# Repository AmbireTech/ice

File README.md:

# Ambire Ice

A Safe-owner signing device: STM32U585 + two secure elements from two vendors,
NXP SE050 and Infineon OPTIGA Trust M, BLE behind a hardware airgap switch, QR
camera, 2.4" capacitive touch display, see-through case. Open hardware; the
firmware starts from a fork of Trezor's.

*Render of the 3D model: the board's back face through the case, with the flame
in silkscreen. The front (screen side) carries no brand at all.*

## Get one

**[ambire.com/ice](https://ambire.com/ice)**: the hardware wallet built for Safe.

- **Batch 2: $159**, limited to 200 devices. Reserve with a **$10 deposit**, which
  counts toward the price. Batch 1 (200 devices) is sold out.
- Delivery expected **within 6 months** of reserving.
- Four colours: Ice Blue, Orange Crush, Atomic Purple, Crystal Clear.
- A Safe signer over USB, Bluetooth or QR. It decodes every Safe action on screen
  (clear signing), blocks unknown DELEGATECALLs, and is ready for a post-quantum key
  on your Safe once chains support it.
- An airgap switch cuts USB data and radio power in hardware; offline, it signs
  over animated QR codes.
- Or build your own: the Gerber, BOM and pick-and-place files for JLCPCB or PCBWay
  are in this repo, and the case, battery-pack tray, joystick cap and airgap slider
  print on a home 3D printer.

Pictures on the site are illustrative; the shipped device may differ in shape and
colour.

**Built to be opened.** The clear case lets you see the board, but you don't
have to take our word for what's inside. Ice is designed to come apart and go
back together at home: undo one small M2 screw and the front hooks off; the
screen lifts off its foam tape and the battery pack comes away from its magnets.
Open it, compare the board with the files in this repo, and close it again.

Hand-routed by [@Ivshti](https://github.com/Ivshti), but component placement is
verified and optimized with
[humanizedKicadAutoRouter](https://github.com/Ivshti/humanizedKicadAutoRouter)
and [KiCadRoutingTools](https://github.com/drandyhaas/KiCadRoutingTools).

## Docs

- [docs/research.md](docs/research.md) — threat landscape 2024–2026, how the
  incumbents are built, why this architecture
- [docs/power-aaa.md](docs/power-aaa.md) — one AAA cell: which cells, how long
  they last, charging only NiMH, the power parts
- [docs/pack.md](docs/pack.md) — v4's battery pack: two AAA cells on a magnetic pogo
  connector pair, what JLC can build, what changes on the board
- [docs/design.md](docs/design.md) — the board, block by block, the case, and
  the bring-up checks that need parts in hand
- [docs/direction.md](docs/direction.md) — open hardware, starting from Trezor's
  firmware (what stands in the way), the configurator and the board print schemes
- [firmware/README.md](firmware/README.md) — the Trezor firmware port: build,
  flash, what changed, bring-up checks
- [docs/board-flow.md](docs/board-flow.md) — netlist → board → checks → order
  set: the commands and the order-time steps
- [art/README.md](art/README.md) — the back print: the flame silkscreen and the
  full-colour print for PCBWay
- [board/experiments/README.md](board/experiments/README.md) — placement
  candidates and how they were judged
- [docs/ambire-signer.html](docs/ambire-signer.html) — the concept page shared
  with the team (3D model, configurator with DIY downloads, clear signing,
  architecture, status); public copy: https://ambiretech.github.io/ice/
  (deployed by `.github/workflows/concept-page.yml`); the old Claude artifact
  link (https://claude.ai/artifact/LLUtmWoVMm4PUxiSL7d5Ad) now points there.
  That page shows proto 0 and stays as it is.
- [docs/v2/index.html](docs/v2/index.html) — the same page for proto 1 (the AAA
  cell, the joystick, the thinner case), with its own model and downloads:
  https://ambiretech.github.io/ice/v2/ (the proto 0 page does not link it)

## Firmware

Trezor's firmware, ported to this board: `firmware/trezor-firmware/` is
[trezor-firmware](https://github.com/trezor/trezor-firmware) with our changes on
top, started from `5fdc180` (2026-10-16). Every Monday a workflow pulls Trezor's
new commits from their `main` into this repo (Trezor → us; nothing goes back to
Trezor), keeps our changes on top, builds, and opens a PR here; the current base
is the first line of `firmware/vendor-pins.txt`. It builds as Trezor's T3T2
model with our own board, `ambire_p0`: our pin map, the display over SPI
(Trezor's is parallel), the FT5426 touch, and a power latch in the boardloader.
Development keys only, for the bench. The secure elements, radio, camera,
charger and battery gauge are not driven yet.

`firmware/docker-build.sh` builds it in Docker with Trezor's own toolchain.
Build, flashing, syncing with Trezor, the full list of changes and the bring-up
checks: [firmware/README.md](firmware/README.md). What is left and why:
[docs/direction.md](docs/direction.md#2-trezor-compatible-start-from-trezors-firmware).

## Board

The board is KiCad (`board/wallet.kicad_pcb`), with the netlist in tscircuit
(`index.circuit.tsx`, `src/blocks/`). How it is checked and turned into an
order: [docs/board-flow.md](docs/board-flow.md). The order set is in
`production/order/` (JLCPCB, and PCBWay for the full-colour back print).

## Similar projects

- [wedgie.dev](https://wedgie.dev)
- [Keycard Shell](https://keycard.tech/products/keycard-shell): an open-source,
  air-gapped signer around a Keycard smart card, with a camera for animated QR
  and no radio
- picowallet (Austin Griffith, 2026-09): the same key model, a P-256 key
  generated in an ATECC608 behind a vault contract, on an RP2350
  (see [docs/research.md](docs/research.md#competitive-notes))

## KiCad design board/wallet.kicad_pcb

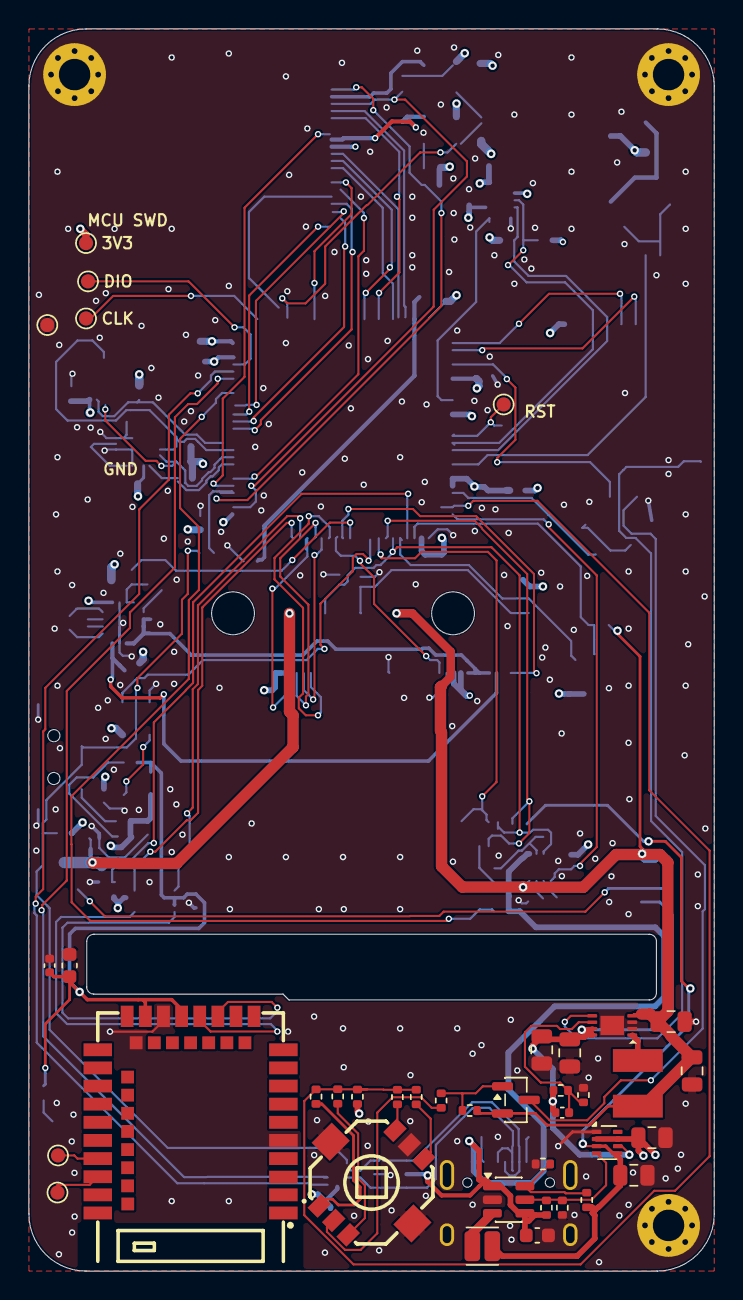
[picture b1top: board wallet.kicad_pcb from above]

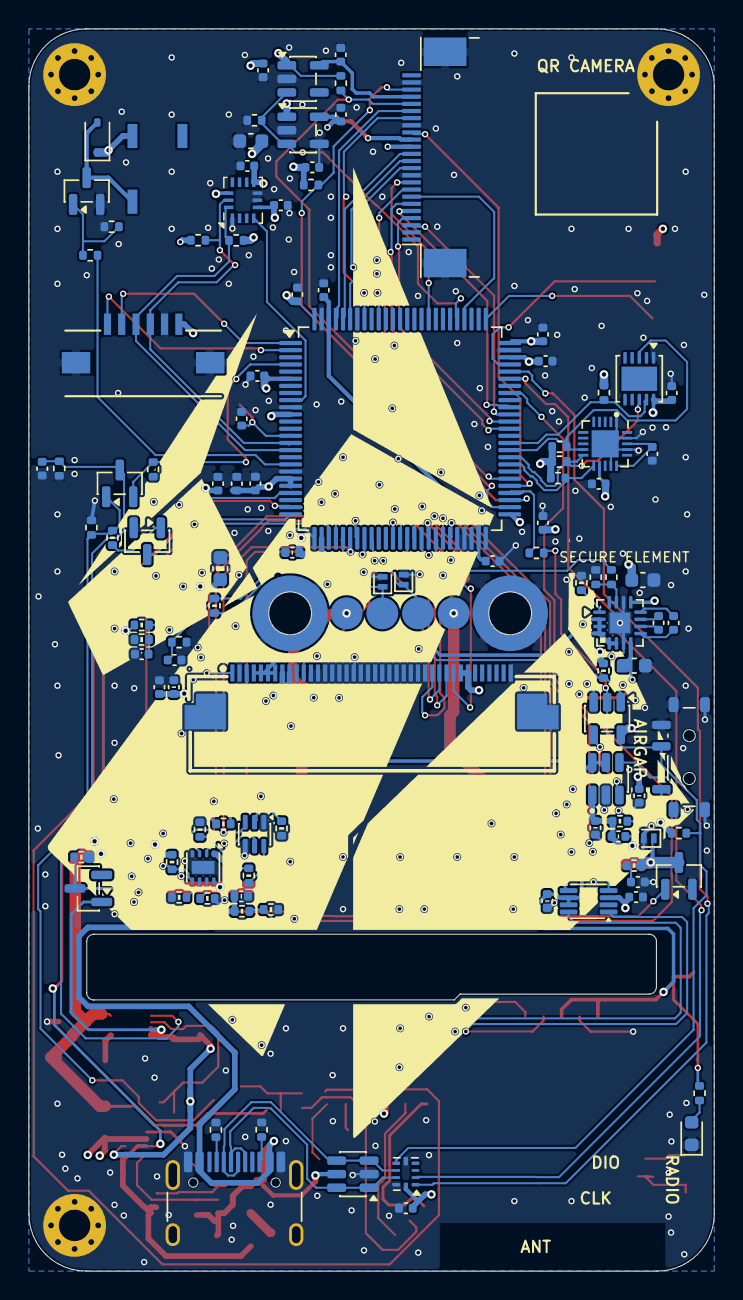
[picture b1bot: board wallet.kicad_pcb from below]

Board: 4 copper layers, 48.0 x 87.0 mm, 157 parts (116 on the bottom side), 108 nets.

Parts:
C_3V3: 22uF; C_0805_2012Metric
C_AVIN: 1uF; C_0402_1005Metric
C_AVOUT: 1uF; C_0402_1005Metric
C_BAT: 10uF; C_0805_2012Metric
C_BLF1, C_BLF2: 470nF; C_0402_1005Metric
C_BLIN: 1uF; C_0603_1608Metric
C_BLOUT: 1uF; C_0603_1608Metric
C_BOOST, C_BOOST2: 47uF; C_0805_2012Metric
C_BUZ: 10uF; C_0603_1608Metric
C_CHGIN: 1uF; C_0402_1005Metric
C_CNS: 100nF; C_0402_1005Metric
C_CS: 100nF; C_0402_1005Metric
C_DOVDD: 100nF; C_0402_1005Metric
C_DVOUT: 1uF; C_0402_1005Metric
C_EN: 1uF; C_0402_1005Metric
C_FFB: 33pF; C_0402_1005Metric
C_IMU1, C_IMU2: 100nF; C_0402_1005Metric
C_IN_BOOST: 22uF; C_0805_2012Metric
C_MS: 100nF; C_0402_1005Metric
C_NOR: 100nF; C_0402_1005Metric
C_NRST: 100nF; C_0402_1005Metric
C_OPT: 100nF; C_0402_1005Metric
C_RADIO1: 10uF; C_0603_1608Metric
C_RADIO2: 100nF; C_0402_1005Metric
C_RCT: 1nF; C_0402_1005Metric
C_RIN: 1uF; C_0402_1005Metric
C_SEIN: 100nF; C_0402_1005Metric
C_SEVCC: 100nF; C_0402_1005Metric
C_TFT1: 1uF; C_0402_1005Metric
C_TFT2: 100nF; C_0402_1005Metric
C_U9A, C_U9B: 100nF; C_0402_1005Metric
C_USB3V3: 22uF; C_0805_2012Metric
C_USBSW: 100nF; C_0402_1005Metric
C_VBAT: 100nF; C_0402_1005Metric
C_VBUS: 4.7uF; C_0603_1608Metric
C_VDD1, C_VDD2, C_VDD3, C_VDD4, C_VDD5: 100nF; C_0402_1005Metric
C_VDD11A, C_VDD11B: 2.2uF; C_0402_1005Metric
C_VDDA1: 1uF; C_0402_1005Metric
C_VDDA2: 100nF; C_0402_1005Metric
C_VDDB: 10uF; C_0603_1608Metric
C_VUSB: 100nF; C_0402_1005Metric
D_BUZ: 1N4148WS; D_SOD-323
D_ESD: USBLC6-2SC6; SOT-23-6
D_OR: BAT54C,215; SOT-23
D_PKMID: PESD5V0S1BL,315; D_SOD-882
D_PKNEG: PESD5V0S1BL,315; D_SOD-882
D_PKNTC: PESD5V0S1BL,315; D_SOD-882
D_RADIO: KT-0603G; LED_0603_1608Metric
D_REVG: BAS116,215; SOT-23
H1, H2, H4: MountingHole_2.2mm_M2_Pad_Via
J1: TYPE-C-31-M-12; USB_C_Receptacle_HRO_TYPE-C-31-M-12_BoardEdge
J_CAM: AFC07-S24FCA-00; Jushuo_AFC07-S24FCA-00_1x24-1MP_P0.50_Horizontal
J_CTP: HC-FPC-1.0-6P-FH20; FPC_HC-FPC-1.0-6P-FH20
J_PK1: J_PK1; Pack_Contact_Pad_D2.235mm
J_PK2: J_PK2; Pack_Contact_Pad_D2.235mm
J_PK3: J_PK3; Pack_Contact_Pad_D2.235mm
J_PK4: J_PK4; Pack_Contact_Pad_D2.235mm
J_TFT: 54132-4062; Molex_54132-4062
LS1: MLT-5020; Buzzer_Huaneng_MLT-5020_5x5.5mm
L_BOOST: WPN4020H2R2MT; L_Sunlord_WPN4020
L_BUCK: CKCSA201610-2.2uH/M; L_Cenker_CKCS201610
MH_PK1, MH_PK2: 9774015243R; Wurth_WA-SMSI_M2_L1.5
Q_BTN: MMBT3904; SOT-23
Q_BUZ: AO3416; SOT-23
Q_CHG: 2N7002DW-7-F; SOT-363_SC-70-6
Q_PWRJ: MMBT3906; SOT-23
Q_REV: AO3416; SOT-23
R_AIRPU: 100k; R_0402_1005Metric
R_AIRS: 1M; R_0402_1005Metric
R_AIRSER: 1k; R_0402_1005Metric
R_BLEN: 1k; R_0402_1005Metric
R_BLPD: 100k; R_0402_1005Metric
R_BLSET: 6.8k; R_0402_1005Metric
R_BTN: 100k; R_0402_1005Metric
R_BTNB: 100k; R_0402_1005Metric
R_BUZG: 100; R_0402_1005Metric
R_BUZPD: 100k; R_0402_1005Metric
R_CAMEN: 100k; R_0402_1005Metric
R_CC1, R_CC2: 5.1k; R_0402_1005Metric
R_CHGHI: 100k; R_0402_1005Metric
R_CHGOFF: 100k; R_0402_1005Metric
R_CNS: 100k; R_0402_1005Metric
R_CS1, R_CS2: 1M; R_0402_1005Metric
R_CSCL: 4.7k; R_0402_1005Metric
R_CSDA: 4.7k; R_0402_1005Metric
R_EN: 1M; R_0402_1005Metric
R_FB1: 1M; R_0402_1005Metric
R_FB2: 562k; R_0402_1005Metric
R_FBU1: 150k; R_0402_1005Metric
R_FBU2: 33k; R_0402_1005Metric
R_HOLD: 1M; R_0402_1005Metric
R_ISET: 3.6k; R_0402_1005Metric
R_ISETH: 1.8k; R_0402_1005Metric
R_JA: 15k; R_0402_1005Metric
R_JB: 27k; R_0402_1005Metric
R_JC: 47k; R_0402_1005Metric
R_JD: 100k; R_0402_1005Metric
R_JPU: 15k; R_0402_1005Metric
R_MS1, R_MS2: 1M; R_0402_1005Metric
R_OPTRST: 100k; R_0402_1005Metric
R_PG: 150k; R_0402_1005Metric
R_PGB: 100k; R_0402_1005Metric
R_PWRJB: 100k; R_0402_1005Metric
R_PWRJBE: 1M; R_0402_1005Metric
R_REVG: 1M; R_0402_1005Metric
R_RLED: 1k; R_0402_1005Metric
R_ROFF: 100k; R_0402_1005Metric
R_SCL: 4.7k; R_0402_1005Metric
R_SDA: 4.7k; R_0402_1005Metric
R_SEENA: 100k; R_0402_1005Metric
R_SESCL: 4.7k; R_0402_1005Metric
R_SESDA: 4.7k; R_0402_1005Metric
R_STAT: 10k; R_0402_1005Metric
R_TMR: 36k; R_0402_1005Metric
R_VB1: 47k; R_0402_1005Metric
R_VB2: 100k; R_0402_1005Metric
R_VSET: 36k; R_0402_1005Metric
SW_AIR: MSK12C02; SW_SPDT_Shouhan_MSK12C02
SW_JOY: SKRHAAE010; SW_ALPS_SKRHAAE010
TP_3V3: TP_3V3; TestPoint_Pad_D1.0mm
TP_GND: TP_GND; TestPoint_Pad_D1.0mm
TP_NRST: TP_NRST; TestPoint_Pad_D1.0mm
TP_RSWCLK: TP_RSWCLK; TestPoint_Pad_D1.0mm
TP_RSWDIO: TP_RSWDIO; TestPoint_Pad_D1.0mm
TP_SWCLK: TP_SWCLK; TestPoint_Pad_D1.0mm
TP_SWDIO: TP_SWDIO; TestPoint_Pad_D1.0mm
U1: BQ25172DSGR; WSON-8-1EP_2x2mm_P0.5mm_EP0.9x1.6mm
U2: LTC3539EDCB-2#TRPBF; LT_DCB8_DFN-8-1EP_2x3mm_P0.45mm
U3: TLV62569PDDCR; SOT-23-6
U4: STM32U585VIT6Q; LQFP-100_14x14mm_P0.5mm
U5: SE050E2HQ1/Z01Z3Z; NXP_SOT1969-1_HX2QFN-20_3x3mm_P0.4mm
U6: TS3USB221ARSER; Texas_UQFN-10_1.5x2mm_P0.5mm
U7: SN74LVC1G02DBVR(UMW); SOT-23-5
U8: TPS22917DBVR; SOT-23-6_PinMarkSouth
U9: TXU0202DCUR; VSSOP-8_2.3x2mm_P0.5mm
U10: TPS2116DRLR; SOT-583-8
U11: E73-2G4M08S1C; Ebyte_E73-2G4M08S1C
U12: ME6211C28M5G-N; SOT-23-5
U13: TPS60230RGTR; VQFN-16-1EP_3x3mm_P0.5mm_EP1.45x1.45mm
U14: TLV70312DBVR; SOT-23-5
U15: BMI270; Bosch_LGA-14_3x2.5mm_P0.5mm
U16: SLS32AIA010MK; DFN-10-1EP_3x3mm_P0.5mm_EP1.7x2.5mm

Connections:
AIRGAP: R_AIRPU.1, R_AIRS.1, SW_AIR.2, U6.6, U7.2
AIRGAP_SENSE: R_AIRS.2, U4.54
AIR_THROW: R_AIRSER.1, SW_AIR.1
BAT: C_BAT.1, C_IN_BOOST.1, J_PK1.1, L_BOOST.1, Q_PWRJ.2, R_CS1.1, R_PWRJBE.1, R_REVG.1, U1.8, U2.4
BAT_N: D_PKNEG.1, J_PK4.1, Q_REV.3, R_CNS.1
BL_A: C_BLOUT.1, J_TFT.3, U13.8
BL_C1N: C_BLF1.2, U13.11
BL_C1P: C_BLF1.1, U13.10
BL_C2N: C_BLF2.2, U13.12
BL_C2P: C_BLF2.1, U13.9
BL_EN: R_BLEN.2, R_BLPD.1, U13.15, U13.16
BL_ISET: R_BLSET.1, U13.1
BL_K: J_TFT.4, J_TFT.5, J_TFT.6, J_TFT.7, U13.2, U13.3, U13.4, U13.5, U13.6
BTN: D_OR.1, Q_PWRJ.3, R_BTN.1, R_BTNB.1
BTN_B: Q_BTN.1, R_BTNB.2
BTN_N: Q_BTN.3, U4.22
BUZZER: R_BUZG.1, U4.18
BUZ_G: Q_BUZ.1, R_BUZG.2, R_BUZPD.1
BUZ_SW: D_BUZ.2, LS1.2, Q_BUZ.3
CAM_AVDD: C_AVOUT.1, J_CAM.21, U12.5
CAM_D0: J_CAM.6, U4.63
CAM_D1: J_CAM.4, U4.64
CAM_D2: J_CAM.3, U4.65
CAM_D3: J_CAM.5, U4.66
CAM_D4: J_CAM.7, U4.79
CAM_D5: J_CAM.9, U4.84
CAM_D6: J_CAM.11, U4.95
CAM_D7: J_CAM.13, U4.96
CAM_DVDD: C_DVOUT.1, J_CAM.15, U14.5
CAM_EN: R_CAMEN.1, U4.80, U12.3, U14.3
CAM_HREF: J_CAM.16, U4.55
CAM_PCLK: J_CAM.8, U4.56
CAM_RST: J_CAM.19, U4.97
CAM_SCL: J_CAM.20, R_CSCL.1, U4.52
CAM_SDA: J_CAM.22, R_CSDA.1, U4.53
CAM_VSYNC: J_CAM.18, U4.93
CAM_XCLK: J_CAM.12, U4.91
CC1: J1.A5, R_CC1.1
CC2: J1.B5, R_CC2.1
CELL_MID: D_PKMID.1, J_PK2.1, R_MS1.1
CELL_MID_SENSE: C_MS.1, R_MS1.2, R_MS2.1, U4.30
CELL_N_SENSE: C_CNS.1, R_CNS.2, U4.29
CELL_SENSE: C_CS.1, R_CS1.2, R_CS2.1, U4.28
CHG_HI: Q_CHG.2, R_CHGHI.1, U4.33
CHG_ISET: R_ISET.1, R_ISETH.1, U1.2
CHG_ISETH: Q_CHG.6, R_ISETH.2
CHG_OFF: Q_CHG.5, R_CHGOFF.1, U4.32
CHG_STAT: R_STAT.1, U1.5, U4.25
CHG_TMR: R_TMR.1, U1.6
CHG_TS: D_PKNTC.1, J_PK3.1, Q_CHG.3, U1.3, U4.31
CHG_VSET: R_VSET.1, U1.7
CTP_INT: J_CTP.5, U4.1
CTP_RST: J_CTP.6, U4.2
FB_BOOST: C_FFB.2, R_FB1.2, R_FB2.1, U2.6
FB_USB: R_FBU1.2, R_FBU2.1, U3.6
GND: C_3V3.2, C_AVIN.2, C_AVOUT.2, C_BAT.2, C_BLIN.2, C_BLOUT.2, C_BOOST.2, C_BOOST2.2, C_BUZ.2, C_CHGIN.2, C_CNS.2, C_CS.2, C_DOVDD.2, C_DVOUT.2, C_EN.2, C_IMU1.2, C_IMU2.2, C_IN_BOOST.2, C_MS.2, C_NOR.2, C_NRST.2, C_OPT.2, C_RADIO1.2, C_RADIO2.2, C_RIN.2, C_SEIN.2, C_SEVCC.2, C_TFT1.2, C_TFT2.2, C_U9A.2, C_U9B.2, C_USB3V3.2, C_USBSW.2, C_VBAT.2, C_VBUS.2, C_VDD1.2, C_VDD2.2, C_VDD3.2, C_VDD4.2, C_VDD5.2, C_VDD11A.2, C_VDD11B.2, C_VDDA1.2, C_VDDA2.2, C_VDDB.2, C_VUSB.2, D_ESD.2, D_PKMID.2, D_PKNEG.2, D_PKNTC.2, D_RADIO.1, H1.1, H2.1, H4.1, J1.A1, J1.A12, J1.B1, J1.B12, J1.SH, J_CAM.10, J_CAM.17, J_CAM.23, J_CAM.MP, J_CTP.2, J_CTP.7, J_CTP.8, J_TFT.2, J_TFT.10, J_TFT.12, J_TFT.13, J_TFT.14, J_TFT.15, J_TFT.16, J_TFT.17, J_TFT.18, J_TFT.19, J_TFT.20, J_TFT.21, J_TFT.22, J_TFT.23, J_TFT.24, J_TFT.25, J_TFT.26, J_TFT.27, J_TFT.28, J_TFT.40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
I2C_SCL: J_CTP.3, R_SCL.1, U4.15, U15.13
I2C_SDA: J_CTP.4, R_SDA.1, U4.16, U15.14
IMU_INT: U4.9, U15.4
JOY_A: R_JA.2, SW_JOY.1
JOY_B: R_JB.2, SW_JOY.4
JOY_C: R_JC.2, SW_JOY.3
JOY_CEN: R_PWRJB.2, SW_JOY.2
JOY_D: R_JD.2, SW_JOY.6
JOY_DIR: R_JA.1, R_JB.1, R_JC.1, R_JD.1, R_JPU.2, U4.24
NRST: C_NRST.1, TP_NRST.1, U4.14
OPTIGA_RST: R_OPTRST.1, U4.61, U16.9
PWRJ_B: Q_PWRJ.1, R_PWRJB.1, R_PWRJBE.2
PWR_EN: C_EN.1, D_OR.3, R_EN.1, U2.5
PWR_HOLD: D_OR.2, R_HOLD.1, U4.4
RADIO_3V3: C_RADIO1.1, C_RADIO2.1, C_U9B.1, R_RLED.1, U8.5, U8.6, U9.6, U9.7, U11.19, U11.23
RADIO_CT: C_RCT.2, U8.4
RADIO_EN: U7.4, U8.3
RADIO_LED_A: D_RADIO.2, R_RLED.2
RADIO_OFF: R_ROFF.1, U4.34, U7.1
RADIO_RX: U9.8, U11.15
RADIO_RXD_MCU: U4.45, U9.4
RADIO_SWCLK: TP_RSWCLK.1, U11.39
RADIO_SWDIO: TP_RSWDIO.1, U11.37
RADIO_TX: U9.1, U11.17
RADIO_TXD_MCU: U4.44, U9.5
REV_G: D_REVG.3, Q_REV.1, R_REVG.2
SE_ENA: R_SEENA.1, U4.58, U5.11
SE_SCL: R_SESCL.1, U4.59, U5.10, U16.8
SE_SDA: R_SESDA.1, U4.60, U5.9, U16.3
SE_VCC: C_SEVCC.1, U5.15, U5.18
SWCLK: TP_SWCLK.1, U4.76
SWDIO: TP_SWDIO.1, U4.72
SW_BOOST: L_BOOST.2, U2.1
SW_USB: L_BUCK.1, U3.3
TFT_BL: R_BLEN.1, U4.37
TFT_CS: J_TFT.31, U4.42
TFT_DC: J_TFT.29, U4.40
TFT_MOSI: J_TFT.32, U4.43
TFT_RST: J_TFT.11, U4.39
TFT_SCK: J_TFT.30, U4.41
TFT_TE: J_TFT.1, U4.38
USB_DN: D_ESD.3, D_ESD.4, J1.A7, J1.B7, U6.7
USB_DP: D_ESD.1, D_ESD.6, J1.A6, J1.B6, U6.8
USB_MCU_DN: U4.70, U6.2
USB_MCU_DP: U4.71, U6.1
USB_PG: R_PG.1, R_PGB.1, U3.5, U10.4
V3V3: C_3V3.1, C_AVIN.1, C_BLIN.1, C_BUZ.1, C_DOVDD.1, C_IMU1.1, C_IMU2.1, C_NOR.1, C_OPT.1, C_RCT.1, C_RIN.1, C_SEIN.1, C_TFT1.1, C_TFT2.1, C_U9A.1, C_USBSW.1, C_VBAT.1, C_VDD1.1, C_VDD2.1, C_VDD3.1, C_VDD4.1, C_VDD5.1, C_VDDA1.1, C_VDDA2.1, C_VDDB.1, C_VUSB.1, D_BUZ.1, J_CAM.14, J_CTP.1, J_TFT.8, J_TFT.9, J_TFT.33, J_TFT.34, LS1.1, R_AIRPU.2, R_AIRSER.2, R_CSCL.2, R_CSDA.2, R_JPU.1, R_OPTRST.2, R_ROFF.2, R_SCL.2, R_SDA.2, R_SEENA.2, R_SESCL.2, R_SESDA.2, R_STAT.2, TP_3V3.1, U4.6, U4.11, U4.20, U4.21, U4.27, U4.51, U4.73, U4.75, U4.100, U5.12, U6.10, U7.5, U8.1, U9.3, U10.2, U10.7, U12.1, U13.13, U14.1, U15.5, U15.8, U15.12, U16.10
V3V3_USB: C_USB3V3.1, L_BUCK.2, R_CHGOFF.2, R_FBU1.1, U10.3, U10.5
VBUS: C_CHGIN.1, C_VBUS.1, D_ESD.5, J1.A4, J1.A9, J1.B4, J1.B9, R_PG.2, R_VB1.1, U1.1, U3.1, U3.4
VBUS_SENSE: R_VB1.2, R_VB2.1, U4.68
VDD11: C_VDD11A.1, C_VDD11B.1, U4.49, U4.98
V_BOOST: C_BOOST.1, C_BOOST2.1, C_FFB.1, D_REVG.1, R_FB1.1, U2.7, U2.8, U10.6

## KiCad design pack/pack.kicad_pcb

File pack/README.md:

# The battery pack's board (v4)

Ambire Ice v4 runs from two AAA cells in a pack that snaps onto its back (why and how:
[../docs/pack.md](../docs/pack.md)). This is the pack's own board: the cells' clips on
one face, four spring pins and the seats of two magnets on the other, the face toward the
device. The magnets, in a printed frame, hold the pack on two steel spacers on the device
board; the pins press on four gold target discs there.

48.0 × 26.6 mm, 2 layers, 0.8 mm thick, ENIG, routed.

*Rendered by KiCad: the outer face (toward the device), and the inner face seen from
behind, mirrored.*

## What is on it

| Part | Face | JLC / LCSC |
|---|---|---|
| Xinyangze YZP0058-20048-02, spring pin, SMD with a peg (1 A) ×4 | outer | C5157341 |
| Radial Magnets 8063, NdFeB N40 magnet, 3.18 × 3.18 mm ×2 (glued into the frame, not assembled by JLC) | outer | DigiKey 469-8063-ND |
| MYOUNG MY-AAA-19-J, AAA clip (−, spring) ×2 | inner | C6937104 |
| MYOUNG MY-AAA-20-J, AAA clip (+) ×2 | inner | C6937107 |
| BHFUSE BSMD1206-075-30V, resettable fuse, 0.75 A hold | inner | C976305 |
| Murata NCP18XH103F03RB, 10 k thermistor (B 3380 K), 0603 | inner | C13564 |
| 1 k resistor, 0402 | inner | C11702 |

The two cells are in series: the south cell's plus goes through the fuse to the BAT+
pin; its minus meets the north cell's plus at the west clips (the mid-point, MID),
which reaches its pin through the 1 k resistor; the north cell's minus is BAT−. The
thermistor sits between the NTC pin and BAT−, for the charger's temperature input. A
coin across the pins never shorts a cell hard: plus to minus runs through the fuse, any
short to MID through the 1 k resistor.

The outer face carries only the pins, the frame's two peg holes, the mid-point's run under
the frame and a BAT− pour. The magnets stand on it over the device's steel, in the
frame's pockets. The pin order lives in one place, `PIN_NETS` in `makePack.py`.

**Where the contacts go.** Over the device's discs and spacers, which lie east-west south
of the device's MCU (x 22.0, y 42.28 in device board coordinates): along the south cell,
the frame's tab east, the four pins in a row under the cell's south flank, plus at the
east end. The clips hold only the cells' ends, so the holes are 5.6 mm from any of their steel, and
the cells lie side by side, 12.8 mm apart: 1.8 mm between neighbouring clips' arms, twice
the ~0.9 mm each arm swings out as a cell goes in (on the east side those arms are the
pack's minus and the south cell's plus, ahead of the fuse). `makePack.py` reads the
contacts' place, the magnets and the clips' steel from the case (`enclosure.json`) and
refuses a hole within 0.3 mm of the steel.

**The small parts** sit in the strip south of the south cell's can, where nothing stands
over them, each straddling its pin's line: the thermistor between BAT− and NTC, the 1 k
resistor at MID, the fuse east of BAT+. The mid-point reaches the resistor from the
south-west clip on the outer face, under the frame.

**The pins' land** is JLC's own (EasyEDA's for C5157341): four quadrant pads in a 2.0 mm
square round a plated hole for the pin's 0.40 mm peg. The hole is 0.50 mm here (EasyEDA
draws 0.40, no room for the peg), with a 1.30 mm ring that joins the quadrants in copper.
Plated, the hole carries each pin to the inner face, where its run starts. The frame's
footprint (`Pack_Frame`, written by `makePack.py`) is its two 1.1 mm peg holes, with the
outline and the magnets on F.Fab; it is out of the BOM and the CPL. The pin's 3D model
(`3d/`, by `connModel.py`) is drawn from Xinyangze's drawing (2015-05-14).

## Files

- `pack.kicad_pcb`, `pack.kicad_pro`: the board and its rules (Power class 0.8 mm for the
  cells, the fuse and the pins; 0.25 mm for the sense lines).
- `makePack.py`: builds the board from scratch from `docs/v4/enclosure/enclosure.json`
  (outline, cells, contacts, magnets, frame) and its own constants (the parts, the copper). After a
  hand edit, edit the board instead.
- `../production/boardOrder.py`: writes `../production/pack-order/` (Gerbers and drill zip,
  JLC BOM and CPL, `stock.txt` with JLC's live stock).

```sh
KICAD_PY=/Applications/KiCad/KiCad.app/Contents/Frameworks/Python.framework/Versions/Current/bin/python3
$KICAD_PY pack/makePack.py                                  # the board (overwrites it)
kicad-cli pcb drc --severity-all pack/pack.kicad_pcb        # as saved, and again with --refill-zones
$KICAD_PY production/boardOrder.py pack/pack.kicad_pcb production/pack-order pack 200   # the order files
```

## Ordering at JLC

- **Assembly:** SMT on **both** faces: the pins on the outer face (top), the clips, the
  fuse, the thermistor and the resistor on the inner face (bottom).
- **Stock:** the pins have 1,216 at JLC (2026-11-01): 304 packs. `stock.txt` marks any
  part whose stock covers fewer than 200 packs as SHORT. The magnets come from DigiKey.
- **Rotations:** check every part in JLC's placement preview before paying. The clips
  carry the same rotation as the device board's (the south cell's exactly so, the
  north cell's turned 180°); the pins are round, so their rotation does not matter. The CPL's rotations are KiCad's, not confirmed by JLC.
- The board is 0.8 mm thick and ENIG: pick both in the order form.

What the checks cover: DRC at every severity (none found, with and without a zone
refill), full connectivity, no stale copper. What they do not: the magnets' hold on the
device's steel spacers and the pins' contact on its discs, the glue, the clips holding cells on a 0.8 mm board, the fuse's heating at full
load, the fit in the tray. These files have not been ordered yet.

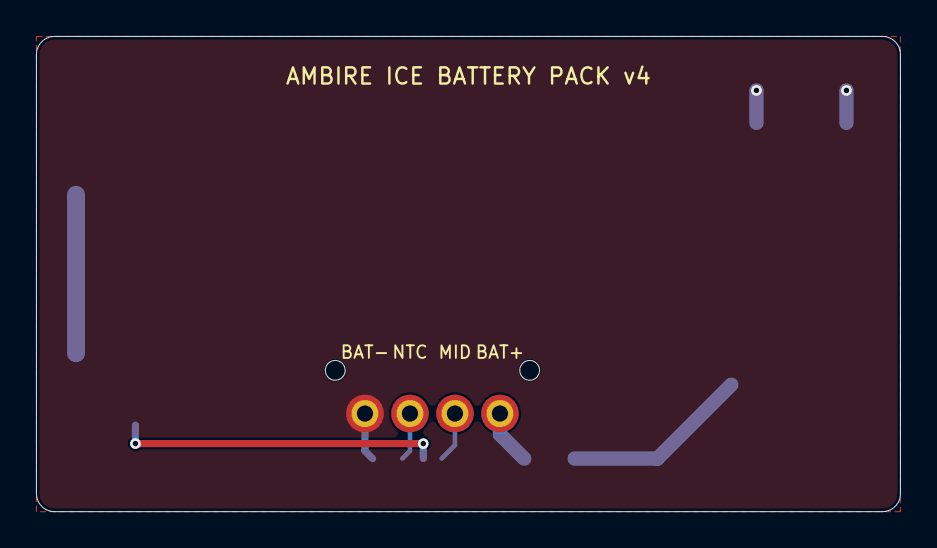
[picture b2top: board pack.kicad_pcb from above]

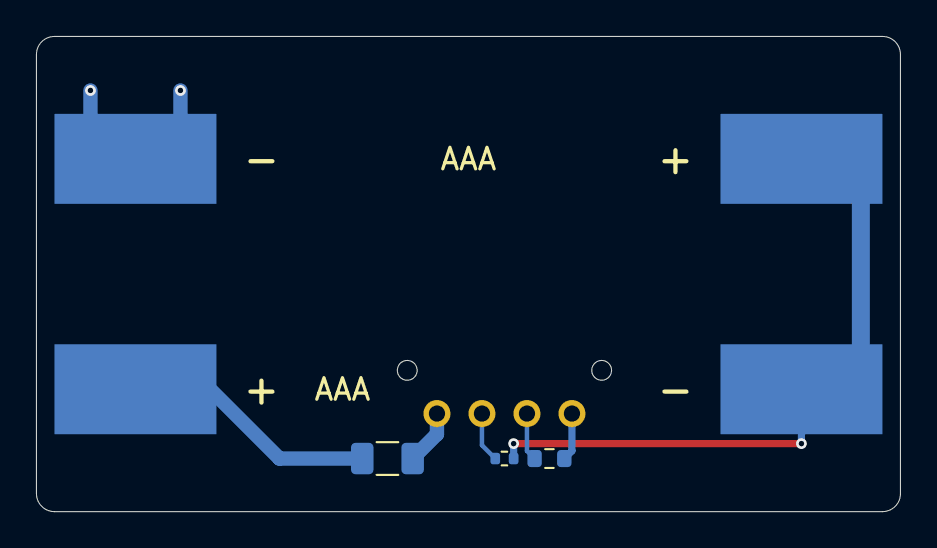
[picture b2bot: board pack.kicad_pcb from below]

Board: 2 copper layers, 48.0 x 26.4 mm, 12 parts (7 on the bottom side), 6 nets.

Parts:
BT_N1, BT_N2: MY-AAA-19-J; Battery_AAA_Clip_MYOUNG_MY-AAA-19-J
BT_P1, BT_P2: MY-AAA-20-J; Battery_AAA_Clip_MYOUNG_MY-AAA-20-J
FR1: frame (print); Pack_Frame
F_BAT: 0.75A hold; Fuse_1206_3216Metric
J_PACK1, J_PACK2, J_PACK3, J_PACK4: YZP0118-20063-02; Xinyangze_YZP0118-20063-02
RT_PACK: 10k NTC B3380; R_0603_1608Metric
R_MID: 1k; R_0402_1005Metric

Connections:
BAT+: F_BAT.1, J_PACK4.1
BAT-: BT_N1.1, J_PACK1.1, RT_PACK.1
CELL+: BT_P2.1, F_BAT.2
MID: BT_N2.1, BT_P1.1, R_MID.1
MID_SENSE: J_PACK3.1, R_MID.2
NTC: J_PACK2.1, RT_PACK.2

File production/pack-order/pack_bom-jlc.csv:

Comment,Designator,Footprint,LCSC Part #
MY-AAA-19-J,"BT_N1,BT_N2",Battery_AAA_Clip_MYOUNG_MY-AAA-19-J,C6937104
MY-AAA-20-J,"BT_P1,BT_P2",Battery_AAA_Clip_MYOUNG_MY-AAA-20-J,C6937107
0.75A hold,F_BAT,Fuse_1206_3216Metric,C976305
YZR0158-20050-04025-01,J_PACK,Xinyangze_YZR0158-20050-04025-01,C5126843
10k NTC B3380,RT_PACK,R_0603_1608Metric,C13564
1k,R_MID,R_0402_1005Metric,C11702

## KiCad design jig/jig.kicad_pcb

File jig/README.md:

# Programming jig

A fixture that programs a bare, assembled device board over SWD, before the screen and
the case go on. One board, one USB-C cable to a computer; no separate debug probe.

The jig sits on a printed base, parts facing up, on four poles through its holes. The
device board goes on **face down**: three of the poles go through its corner holes and
carry it 5 mm above the jig, and seven spring pins press up into its programming pads (3.3 V, ground, SWDIO, SWCLK and reset for the MCU; SWDIO and
SWCLK for the radio). The jig is a USB debug probe: an RP2040 running Raspberry Pi's open
debugprobe firmware, which speaks CMSIS-DAP. It also powers the board while it is
programmed. The USB-C, the two switches and the two lights sit on a strip beside the
board, where they stay in reach and in sight.

The repo's SWD tool works with it as it is: `firmware/swd.py --probe cmsis-dap …`.

**Ordered on 2026-11-01** (the Gerbers of c593d1c). From then on the device board's
programming pads and its holes H1, H2, H4 are **frozen** where `jig/frozen.json` has them:
their footprints are locked in KiCad, and the device board's pre-fab checks fail if any of
them moves. Moving one means a new jig.

## What it is made of

| Part | How many | Where from |
|---|---|---|
| Jig board, 62 × 93 mm, 4 layers, 1.6 mm, parts on one face | 1 | JLC: `production/jig-order/` |
| Base: a plate with four poles | 1 | printed: `jig/out/base.stl` |
| Lid: rests on the board's three hole rings | 1 | printed: `jig/out/lid.stl` |
| A weight of about 300 g (a phone, a small bag of coins) | 1 | to hand |

Every electronic part is JLC stock. The seven spring pins (Xinyangze YZP0063-20068-01)
work at 5.0 mm, 25 g each.

## Putting it together

Print the base and the lid, ideally in resin (JLC3DP's SLA, or any resin printer): the
poles end in 2 mm pins. An FDM print works too, poles standing up, but the pins are
fragile. Drop the jig onto the base's four poles, parts face up: it rests on the poles'
wide feet. Nothing else holds it.

The weight is needed, not optional: the seven spring pins push up with about 175 g, and a
board weighs about 15 g. Without it the board floats on the pins, a millimetre above the
poles, touching its pads with almost no force.

## First use: load the probe's firmware

1. Download `debugprobe_on_pico.uf2` from Raspberry Pi's debugprobe releases
   (github.com/raspberrypi/debugprobe). The jig is wired exactly as that build expects.
2. Plug the jig into a computer. A new jig has an empty flash and shows up as a USB drive
   called RPI-RP2. Copy the file onto it. The drive disappears and the green USB light
   comes on: the probe is ready.
3. To load firmware again later, bridge the two BOOT pads (tweezers) while plugging in.
   Do it with no board on the jig: the pads are under it.

## Programming a board

1. Lay the board **face down** on the jig, its three corner holes over the three poles'
   pins. Put the lid on (its three holes over the same pins) and the weight on the lid.
2. Slide **TARGET 3V3** to ON. The red light shows the board is powered.
3. **The MCU:** selector to **MCU**, then for example

   ```sh
   firmware/swd.py --probe cmsis-dap info
   firmware/swd.py --probe cmsis-dap flash
   ```

4. **The radio** (after the MCU's firmware runs: the MCU switches the radio's power on):
   selector to **RADIO**, then `firmware/swd.py --probe cmsis-dap radio-info` and
   `radio-flash`.
5. TARGET 3V3 to OFF, weight and lid off, board out.

Keep TARGET 3V3 **off** whenever the board runs from its own battery pack or its own USB.

## Check once, on the first jig

- **Switch directions.** The labels assume a slide switch connects the side its knob is
  on. With the jig unplugged, check with a meter: selector at MCU, the SWDIO spring pin
  connects to the selector's middle pin; TARGET 3V3 at ON, the 3.3 V spring pin reads 3.3 V
  with USB in.
- **Registration.** Each spring pin's tip should land in the middle of its pad: look at
  the marks they leave on a first board. The poles locate both boards, so a print that is
  a little off moves them together; a pin that is loose in a hole is the thing to watch.
- **SWD speed.** `swd.py` defaults to 1 MHz for flying leads; on the jig a faster clock
  (`--khz 4000`) should work, untried.

## Making the board

```sh
KICAD_PY=/Applications/KiCad/KiCad.app/Contents/Frameworks/Python.framework/Versions/Current/bin/python3
$KICAD_PY jig/makeJig.py --check                           # do the device board's pads and holes still match?
$KICAD_PY jig/makeJig.py                                   # placed, planes drawn, not routed
$KICAD_PY ../../tools/humanRouter/run.py jig/jig.kicad_pcb --out /tmp/jigroute     # route it
$KICAD_PY scripts/tidyDefects.py /tmp/jigroute/jig.kicad_pcb jig/jig.kicad_pcb     # stubs out
kicad-cli pcb drc --severity-all jig/jig.kicad_pcb         # as saved, and again with --refill-zones
$KICAD_PY production/boardOrder.py jig/jig.kicad_pcb production/jig-order jig 5
../../.venv-enclosure/bin/python jig/makeFixture.py --check   # base and lid; overlaps with both boards
```

`makeJig.py` holds the jig's board: the probe's parts and nets and the pins over the
device's pads; `makeFixture.py` the printed base and lid; `geometry.py` the numbers both
share (the holes, the heights, the pole sizes). It overwrites the board. It first reads the
device board and refuses to build when a programming pad or one of the three holes has
moved, or when two pads sit closer than 2.5 mm (the pins' flanges): change the jig's
numbers to the board's, rebuild, route, and recut its order files.

## Ordering at JLC

- 4 layers, 1.6 mm, any colour; assembly on **one** face: every part is on the bottom
  layer (the parts face).
- Check every part's rotation in JLC's placement preview before paying: the RP2040's pin 1,
  the crystal, the two regulators, the USB-C, the ESD clamp, the two LEDs' polarity and
  both switches.
- The spring pins: JLC had 401 on 2026-11-01; one jig takes seven.

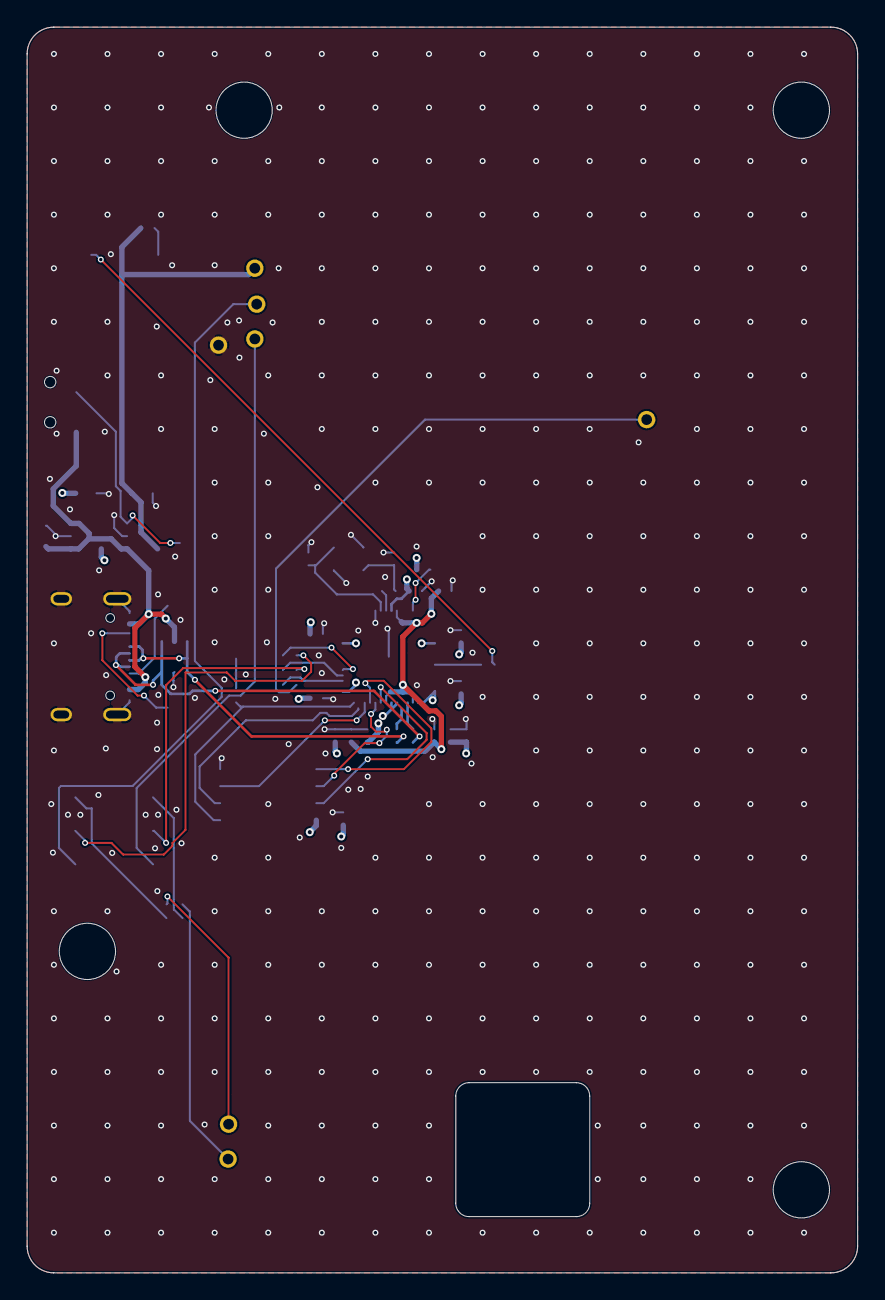
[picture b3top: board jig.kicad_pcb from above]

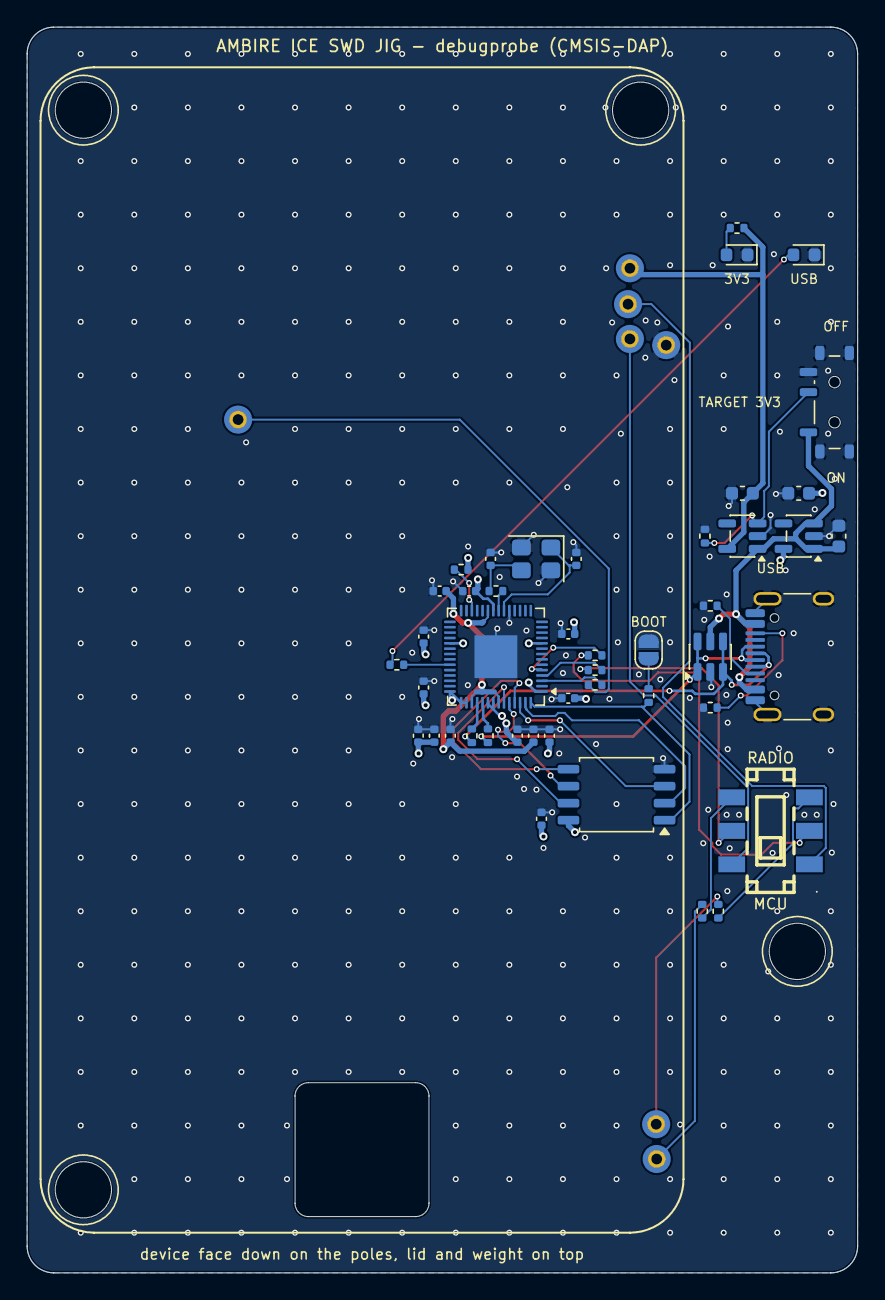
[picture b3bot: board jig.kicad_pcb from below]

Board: 4 copper layers, 62.0 x 93.0 mm, 56 parts (56 on the bottom side), 38 nets.

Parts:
C_3V3P: 10uF; C_0603_1608Metric
C_AV: 100nF; C_0402_1005Metric
C_DV23, C_DV50: 100nF; C_0402_1005Metric
C_FL: 100nF; C_0402_1005Metric
C_IO1, C_IO10, C_IO22, C_IO33, C_IO42, C_IO49: 100nF; C_0402_1005Metric
C_TGT: 10uF; C_0603_1608Metric
C_UV: 100nF; C_0402_1005Metric
C_VBUS: 10uF; C_0603_1608Metric
C_VRI: 1uF; C_0402_1005Metric
C_VRO: 1uF; C_0402_1005Metric
C_XI: 15pF; C_0402_1005Metric
C_XO: 15pF; C_0402_1005Metric
D_ESD: USBLC6-2SC6; SOT-23-6
D_TGT: red; LED_0603_1608Metric
D_USB: green; LED_0603_1608Metric
H_1, H_2, H_4, H_5: pole; Jig_Hole_Pole_4.2mm
JP_BOOT: SolderJumper-2_P1.3mm_Open_RoundedPad1.0x1.5mm
J_USB: TYPE-C-31-M-12; USB_C_Receptacle_HRO_TYPE-C-31-M-12_BoardEdge
P_3V3: YZP0063-20068-01; Xinyangze_YZP0063-20068-01
P_GND: YZP0063-20068-01; Xinyangze_YZP0063-20068-01
P_NRST: YZP0063-20068-01; Xinyangze_YZP0063-20068-01
P_RSWCLK: YZP0063-20068-01; Xinyangze_YZP0063-20068-01
P_RSWDIO: YZP0063-20068-01; Xinyangze_YZP0063-20068-01
P_SWCLK: YZP0063-20068-01; Xinyangze_YZP0063-20068-01
P_SWDIO: YZP0063-20068-01; Xinyangze_YZP0063-20068-01
R_BOOT: 1k; R_0402_1005Metric
R_CC1, R_CC2: 5.1k; R_0402_1005Metric
R_CE: 100k; R_0402_1005Metric
R_DN: 27; R_0402_1005Metric
R_DP: 27; R_0402_1005Metric
R_LT: 1k; R_0402_1005Metric
R_LU: 1k; R_0402_1005Metric
R_NRST: 1k; R_0402_1005Metric
R_RSWC: 1k; R_0402_1005Metric
R_RSWD: 1k; R_0402_1005Metric
R_RUN: 10k; R_0402_1005Metric
R_SWC: 100; R_0402_1005Metric
R_SWD: 100; R_0402_1005Metric
R_XO: 1k; R_0402_1005Metric
SW_PWR: MSK12C02; SW_SPDT_Shouhan_MSK12C02
SW_SEL: K3-2235S-K1; SW_DPDT_Hroparts_K3-2235S-K1
U1: RP2040; QFN-56-1EP_7x7mm_P0.4mm_EP3.2x3.2mm
U2: W25Q16JVSSIQ; SOIC-8_5.3x5.3mm_P1.27mm
U_LP: ME6211C33; SOT-23-5
U_LT: ME6211C33; SOT-23-5
Y1: 12MHz; Crystal_SMD_3225-4Pin_3.2x2.5mm

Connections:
BOOT_R: JP_BOOT.1, R_BOOT.2
CC1: J_USB.A5, R_CC1.1
CC2: J_USB.B5, R_CC2.1
CE_TGT: R_CE.1, SW_PWR.2, U_LT.3
GND: C_3V3P.2, C_AV.2, C_DV23.2, C_DV50.2, C_FL.2, C_IO1.2, C_IO10.2, C_IO22.2, C_IO33.2, C_IO42.2, C_IO49.2, C_TGT.2, C_UV.2, C_VBUS.2, C_VRI.2, C_VRO.2, C_XI.2, C_XO.2, D_ESD.2, D_TGT.1, D_USB.1, JP_BOOT.2, J_USB.A1, J_USB.A12, J_USB.B1, J_USB.B12, J_USB.SH, P_GND.1, R_CC1.2, R_CC2.2, R_CE.2, SW_PWR.3, SW_PWR.SH, U1.19, U1.57, U2.4, U_LP.2, U_LT.2, Y1.2, Y1.4
LED_TGT_A: D_TGT.2, R_LT.2
LED_USB: R_LU.1, U1.37
LED_USB_A: D_USB.2, R_LU.2
MCU_SWCLK: P_SWCLK.1, SW_SEL.6
MCU_SWDIO: P_SWDIO.1, SW_SEL.1
NRST: P_NRST.1, R_NRST.2
PRB_NRST: R_NRST.1, U1.3
PRB_SWCLK: R_SWC.1, U1.4
PRB_SWDIO: R_SWD.1, U1.5
QSPI_SCLK: U1.52, U2.6
QSPI_SD0: U1.53, U2.5
QSPI_SD1: U1.55, U2.2
QSPI_SD2: U1.54, U2.3
QSPI_SD3: U1.51, U2.7
QSPI_SS: R_BOOT.1, U1.56, U2.1
RAD_SWCLK: P_RSWCLK.1, R_RSWC.2
RAD_SWCLK_S: R_RSWC.1, SW_SEL.4
RAD_SWDIO: P_RSWDIO.1, R_RSWD.2
RAD_SWDIO_S: R_RSWD.1, SW_SEL.3
RUN: R_RUN.2, U1.26
SWCLK_P: R_SWC.2, SW_SEL.5
SWDIO_P: R_SWD.2, SW_SEL.2
USBR_DN: R_DN.2, U1.46
USBR_DP: R_DP.2, U1.47
USB_DN: D_ESD.3, D_ESD.4, J_USB.A7, J_USB.B7, R_DN.1
USB_DP: D_ESD.1, D_ESD.6, J_USB.A6, J_USB.B6, R_DP.1
V1V1: C_DV23.1, C_DV50.1, C_VRO.1, U1.23, U1.45, U1.50
V3V3_PROBE: C_3V3P.1, C_AV.1, C_FL.1, C_IO1.1, C_IO10.1, C_IO22.1, C_IO33.1, C_IO42.1, C_IO49.1, C_UV.1, C_VRI.1, R_RUN.1, U1.1, U1.10, U1.22, U1.33, U1.42, U1.43, U1.44, U1.48, U1.49, U2.8, U_LP.5
V3V3_TGT: C_TGT.1, P_3V3.1, R_LT.1, U_LT.5
VBUS: C_VBUS.1, D_ESD.5, J_USB.A4, J_USB.A9, J_USB.B4, J_USB.B9, SW_PWR.1, U_LP.1, U_LP.3, U_LT.1
XIN: C_XI.1, U1.20, Y1.1
XOUT: R_XO.1, U1.21
XOUT_R: C_XO.1, R_XO.2, Y1.3

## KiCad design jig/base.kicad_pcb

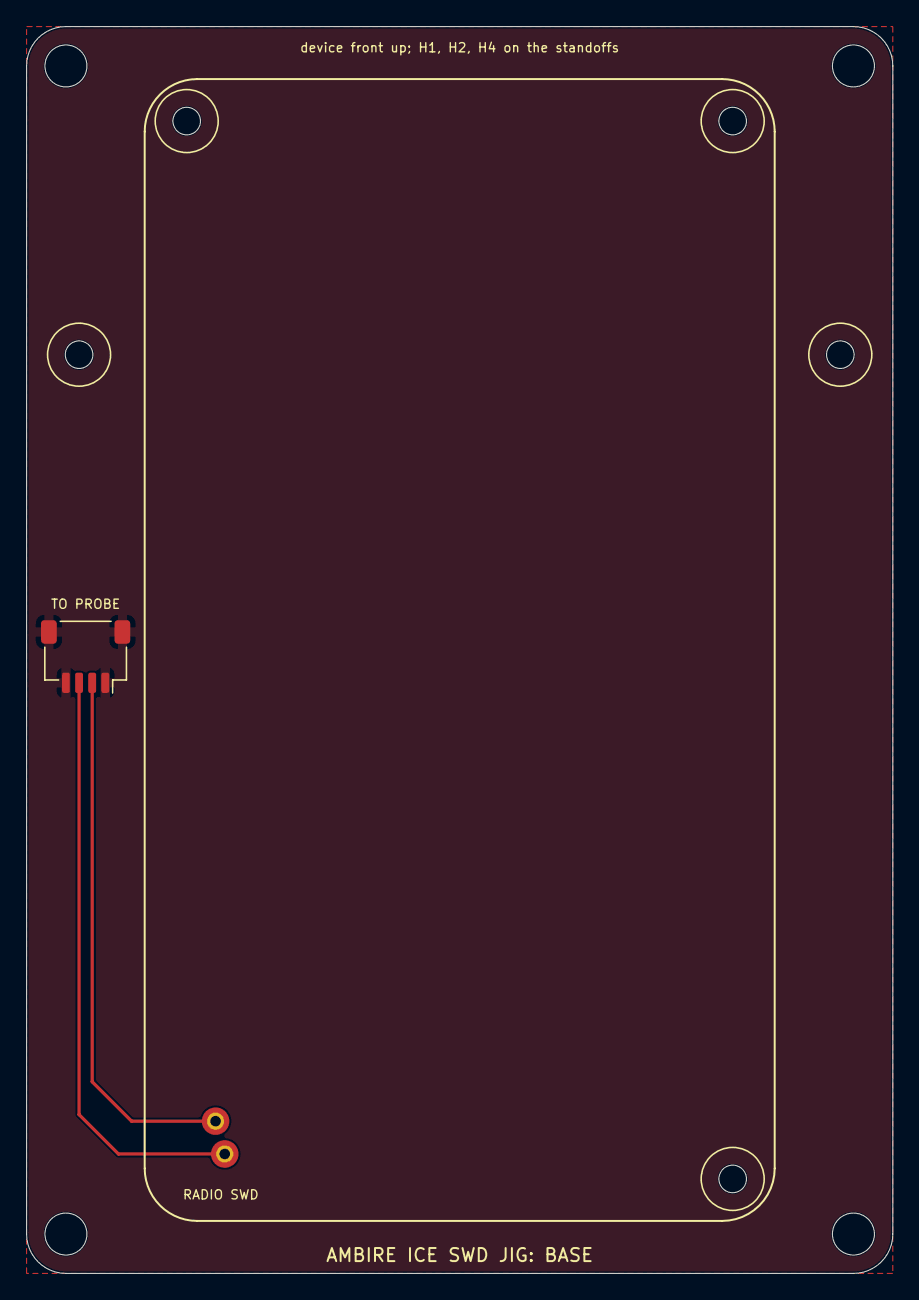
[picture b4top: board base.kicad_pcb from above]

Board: 2 copper layers, 66.0 x 95.0 mm, 12 parts (0 on the bottom side), 3 nets.

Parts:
H_1, H_2, H_4: M2 hole; Jig_Hole_M2_NPTH
H_F1, H_F2, H_F3, H_F4: M3 foot; Jig_Hole_M3_Foot
H_P1, H_P2: M2 hole; Jig_Hole_M2_NPTH
J_RAD: SM04B-SRSS-TB; JST_SH_SM04B-SRSS-TB_1x04-1MP_P1.00mm_Horizontal
P_RSWCLK: YZP0063-20068-01; Xinyangze_YZP0063-20068-01
P_RSWDIO: YZP0063-20068-01; Xinyangze_YZP0063-20068-01

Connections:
GND: J_RAD.1, J_RAD.4, J_RAD.MP
RAD_SWCLK: J_RAD.3, P_RSWCLK.1
RAD_SWDIO: J_RAD.2, P_RSWDIO.1

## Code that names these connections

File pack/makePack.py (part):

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  B (inner face): two AAA cells east-west in series, in MYOUNG clips copied from the
    device board (the south cell as proto 1's cell sat, + east; the north cell turned
    end for end, + west; the west clips are the mid-point); the fuse, the thermistor and
    the mid-point's series resistor beside the pins.

pcbnew: one LoadBoard per process. The board is started as a minimal file beside
pack.kicad_pro (so it gets the pack's rules), loaded once, built, zones filled, saved.
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CONN_PAD = 1.5                            # a pin's plated peg hole's ring on the inner face (see the footprint)
JOINT_CLR = 0.3                           # a hole's ring to a clip's steel, at least
PITCH = 2.5
PIN_NETS = ["BAT-", "NTC", "MID_SENSE", "BAT+"]   # west to east: the one place the pin order lives
PIN_XS = [round(CONN_X + (i - 1.5) * PITCH, 3) for i in range(4)]
PIN = dict(zip(PIN_NETS, PIN_XS))
if sorted(round(x, 3) for x, _ in _PACK["pins"]["xy"]) != PIN_XS or any(abs(y - CONN_Y) > 0.01 for _, y in _PACK["pins"]["xy"]):
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# ── parts ───────────────────────────────────────────────────────────────────
# (ref, library, footprint, value, LCSC, mpn, at, rotation, (west/north pad's net, east/south pad's net))
# In the strip south of the south cell's can, where nothing stands over them (the case
# checks it, PACK_SMALL), each straddling its pin's line: the thermistor between BAT- and
# NTC, the resistor at MID, the fuse east of BAT+.
_SY = round(CONN_Y + 2.5, 3)              # the strip's centre line
SMALL = [
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# ── copper, by hand: (net, layer, width, points) and (net, x, y) vias ───────
# From each small part up to its pin; CELL+ from the fuse's east end to the south-east
# clip; the mid-point from the south-west clip on the outer face, under the frame, to the
# resistor; BAT- reaches the outer face's pour (the BAT- pin's pads are in it). Each run
# ends at its pin's plated peg hole on the inner face.
_cn, _cs = CELL_YS
_fx, _rx, _tx = (p[6][0] for p in SMALL)          # the fuse's, the resistor's, the thermistor's x
_up = lambda x0, x1: [(x0, _SY), (x1, _SY - abs(x1 - x0)), (x1, CONN_Y)]   # 45 deg off the pad, then up to the pin
_mv = round(CONN_Y + 1.67, 3)                        # MID's crossing on the outer face, between the joints and the strip
TRACKS = [
    ("BAT+", "B", W_PWR, _up(_fx - 1.4, PIN["BAT+"])),
    ("MID_SENSE", "B", W_SIG, _up(_rx + 0.51, PIN["MID_SENSE"])),
    ("NTC", "B", W_SIG, _up(_tx + 0.825, PIN["NTC"])),
    ("BAT-", "B", W_FAN, _up(_tx - 0.825, PIN["BAT-"])),
    ("CELL+", "B", W_PWR, [(_fx + 1.4, _SY), (34.5, _SY), (38.6, _SY - 4.1)]),   # into the south-east clip's pad
    ("BAT-", "B", W_PWR, [(40.0, _cn - 2.0), (40.0, _cn - 3.8)]),    # north cell - -> vias into the pour, north
    ("BAT-", "B", W_PWR, [(45.0, _cn - 2.0), (45.0, _cn - 3.8)]),    # of its clip
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
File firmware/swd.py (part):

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        """{line name: (chip, offset)} from gpioinfo on the host (libgpiod v1 and v2 print alike)."""
        out = self.ssh("gpioinfo")
        if out.returncode != 0:
            die(f"gpioinfo on {self.host} failed ({out.stderr.strip()}): run `setup` first")
        lines, chip = {}, None
        for l in out.stdout.splitlines():
            m = re.match(r"^gpiochip(\d+)", l)
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                         for c, o in self._pins)

    def command(self, a):
        """An OpenOCD argv, run here or on the probe board (pins released after)."""
        if not self.host:
            return a
        return ["ssh", self.host, f"{shlex.join(a)}; rc=$?; {self.release_pins() or 'true'}; exit $rc"]
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        if not self.host:
            die("setup is for a Linux board as the probe: it installs OpenOCD there")
        pins = " ".join(GPIO_PROBES[self.args.probe])
        p = subprocess.run(["ssh", self.host, "command -v openocd >/dev/null && command -v gpioinfo >/dev/null || "
                            "(sudo apt-get update && sudo apt-get install -y openocd gpiod) || exit 1; "
                            # BeagleBone: make sure the pins are in GPIO mode
                            f"if command -v config-pin >/dev/null; then for p in {pins}; do config-pin $p gpio; done; fi; "
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            return
        pa, pe = r2["pa_idr"], r2["pe_idr"]
        hold_out = (r2["pe_moder"] >> 10 & 3) == 1
        print(f"pins      PWR_HOLD (PE5) {'output ' + str(r2['pe_odr'] >> 5 & 1) if hold_out else 'NOT an output'}"
              f"   -> the power latch {'holds' if hold_out and r2['pe_odr'] >> 5 & 1 else 'is NOT held'}")
        def pin(idr, moder, n, label, meaning):
            # U5 pins reset to analog mode, where IDR reads 0 whatever the pin carries
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                print(f"          {label} not read: still in analog mode (no stage set it up yet)")
            else:
                print(f"          {label} {idr >> n & 1}  ({meaning})")
        pin(pa, r2["pa_moder"], 9, "VBUS_SENSE (PA9)", "1 = USB power present")
        pin(pe, r2["pe_moder"], 7, "AIRGAP_SENSE (PE7)", "1 = airgapped: USB data and radio off")
        pull = r2["pa_pupdr"] & 3
        pin(pa, r2["pa_moder"], 0, "BTN_N (PA0)", "0 = button pressed"
            + ("" if pull == 1 else "; no pull-up set on PA0, so a released button floats"))

    # --- trustzone --------------------------------------------------------
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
